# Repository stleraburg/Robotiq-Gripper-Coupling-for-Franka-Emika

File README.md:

The coupling consists of two parts: **electrical** and **mechanical**. 

### Electrical Part
PCB designed in KiCad 6.0 software represents electrical part. The gripper uses power of 24V (+ -) and serial RS485 communication (485+, 485- and 485 GND). The Gripper interfaces with its coupling via a 10-spring pin (pogo) connector located on its outer surface. The power pins are traced to their respective connector, as are the RS-485 communication pins, according to this configuration. 

The PCB layout is depicted below. 

I used U2D2 ROBOTIS RS485-USB communication converter to connect the gripper to the PC/robot controller. 

### Mechanical Part
There are three mechanical parts designed in Fusion360. The first one is attached to Franka, next a PCB holder goes, and finally the part to attach the Robotiq gripper. PCB is located between the PCB holder and the gripper part. All parts are screwed with M6 bolts.

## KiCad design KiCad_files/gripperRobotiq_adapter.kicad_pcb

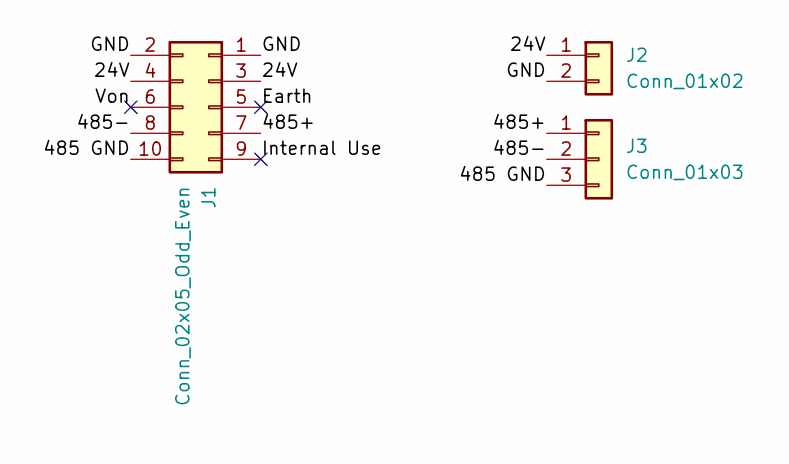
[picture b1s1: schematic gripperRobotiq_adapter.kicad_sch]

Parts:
J1: Conn_02x05_Odd_Even; PinHeader_2x05_P2.54mm_Vertical
J2: Conn_01x02; TerminalBlock_Phoenix_PT-1,5-2-5.0-H_1x02_P5.00mm_Horizontal
J3: Conn_01x03; PinHeader_1x03_P2.54mm_Vertical

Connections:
/24V: J1.3, J1.4, J2.1
/485 GND: J1.10, J3.3
/485+: J1.7, J3.1
/485-: J1.8, J3.2
/Earth: J1.5
/GND: J1.1, J1.2, J2.2
/Internal Use: J1.9
/Von: J1.6

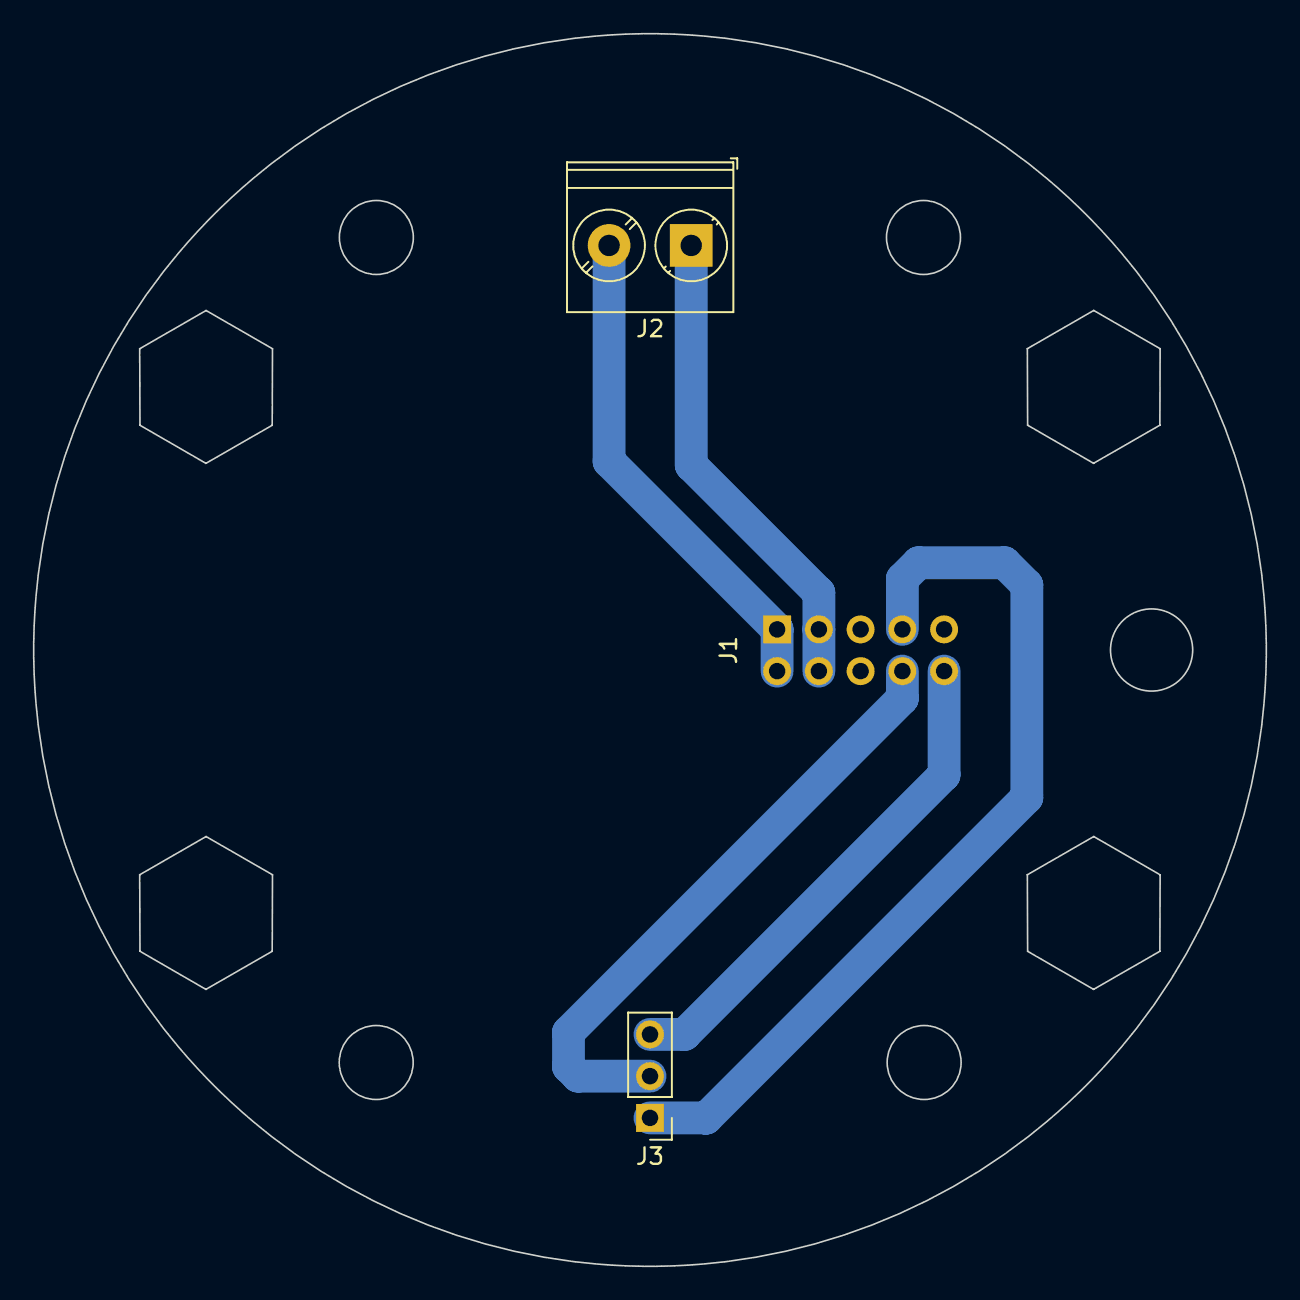
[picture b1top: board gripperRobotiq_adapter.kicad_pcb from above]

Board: 2 copper layers, 75.0 x 75.0 mm, 3 parts (1 on the bottom side), 5 nets.

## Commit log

2024-05-10 push files and images
2024-05-10 add stl files
2024-05-11 push PCB files
2024-05-11 push pinout view image
2024-05-11 push rendered 3D images
2024-05-13 push Fusion360 files: Franka part as a separate part!
